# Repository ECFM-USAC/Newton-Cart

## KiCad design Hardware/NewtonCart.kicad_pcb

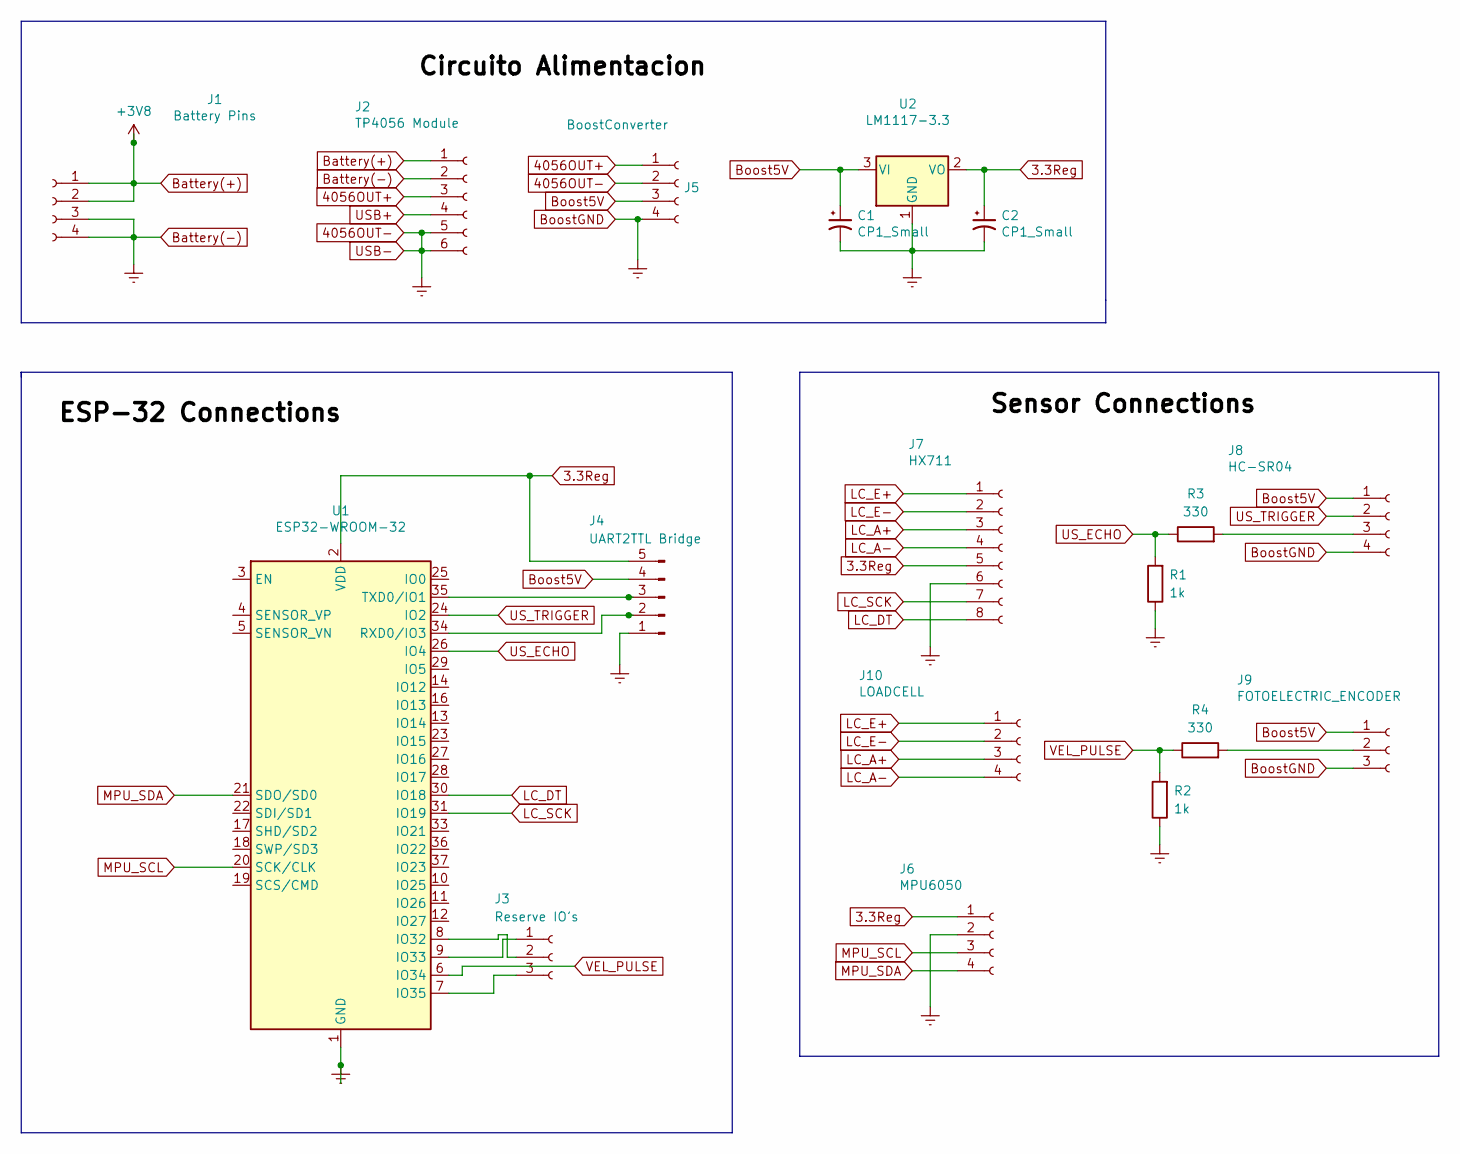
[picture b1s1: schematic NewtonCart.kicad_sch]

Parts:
C1, C2: CP1_Small; R_Axial_DIN0204_L3.6mm_D1.6mm_P5.08mm_Horizontal
J1: Battery Pins; PinHeader_1x04_P2.54mm_Vertical
J2: TP4056 Module; 18650 TP4056 Module
J3: Reserve IO's; PinHeader_1x03_P2.54mm_Vertical
J4: UART2TTL Bridge; PinHeader_1x05_P2.54mm_Vertical
J5: BoostConverter; 5-12V BoostConverter
J6: MPU6050; MPU 6050 Module
J7: HX711; HX711 Loadcell ADC
J8: HC-SR04; PinHeader_1x04_P2.54mm_Vertical
J9: FOTOELECTRIC_ENCODER; PinHeader_1x03_P2.54mm_Vertical
J10: LOADCELL; PinHeader_1x04_P2.54mm_Vertical
R1, R2: 1k; R_Axial_DIN0309_L9.0mm_D3.2mm_P12.70mm_Horizontal
R3, R4: 330; R_Axial_DIN0309_L9.0mm_D3.2mm_P12.70mm_Horizontal
U1: ESP32-WROOM-32
U2: LM1117-3.3; TO-220-3_Vertical

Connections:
3.3Reg: C2.1, J4.5, J6.1, J7.5, U1.2 (VDD), U2.2 (VO)
4056OUT+: J2.3, J5.1
4056OUT-: C1.2, C2.2, J1.3, J1.4, J2.2, J2.5, J2.6, J4.1, J5.2, J5.4, J6.2, J7.6, J8.4, J9.3, R1.1, R2.1, U1.1 (GND), U1.15 (GND), U1.38 (GND), U1.39 (GND), U2.1 (GND)
Battery(+): J1.1, J1.2, J2.1
Boost5V: C1.1, J4.4, J5.3, J8.1, J9.1, U2.3 (VI)
LC_A+: J7.3, J10.3
LC_A-: J7.4, J10.4
LC_DT: J7.8, U1.30 (IO18)
LC_E+: J7.1, J10.1
LC_E-: J7.2, J10.2
LC_SCK: J7.7, U1.31 (IO19)
MPU_SCL: J6.3, U1.20 (SCK/CLK)
MPU_SDA: J6.4, U1.21 (SDO/SD0)
unnamed: J3.3, U1.7 (IO35)
unnamed: J4.2, U1.34 (RXD0/IO3)
unnamed: J4.3, U1.35 (TXD0/IO1)
unnamed: J8.3, R3.2
unnamed: J9.2, R4.2
unnamed: J3.2, U1.8 (IO32)
unnamed: J3.1, U1.9 (IO33)
USB+: J2.4
US_ECHO: R1.2, R3.1, U1.26 (IO4)
US_TRIGGER: J8.2, U1.24 (IO2)
VEL_PULSE: R2.2, R4.1, U1.6 (IO34)

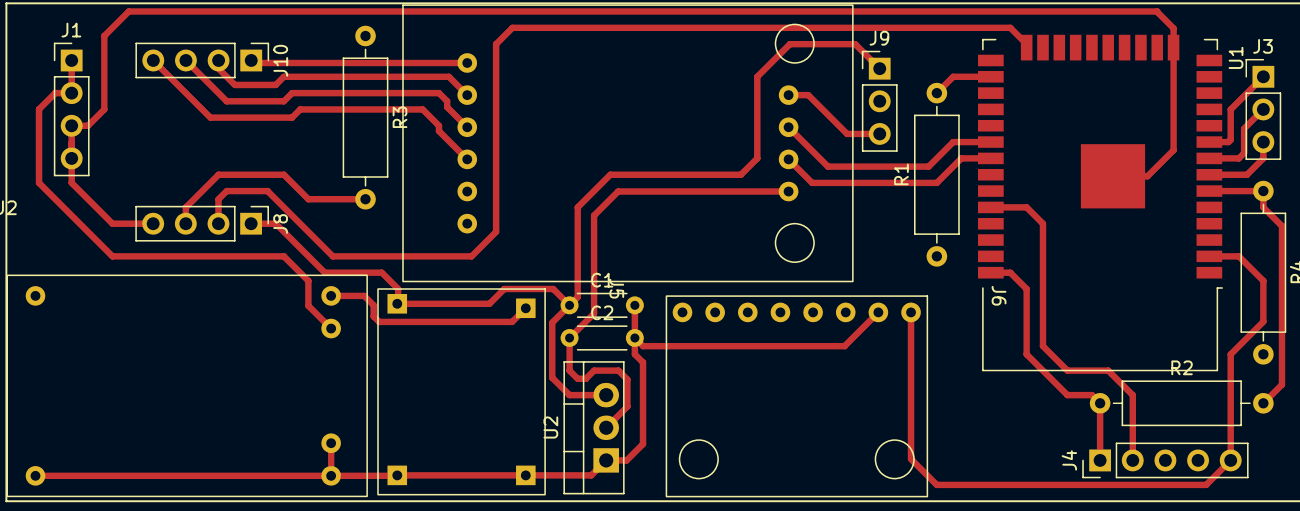
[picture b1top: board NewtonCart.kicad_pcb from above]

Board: 2 copper layers, 18 parts (0 on the bottom side), 23 nets.

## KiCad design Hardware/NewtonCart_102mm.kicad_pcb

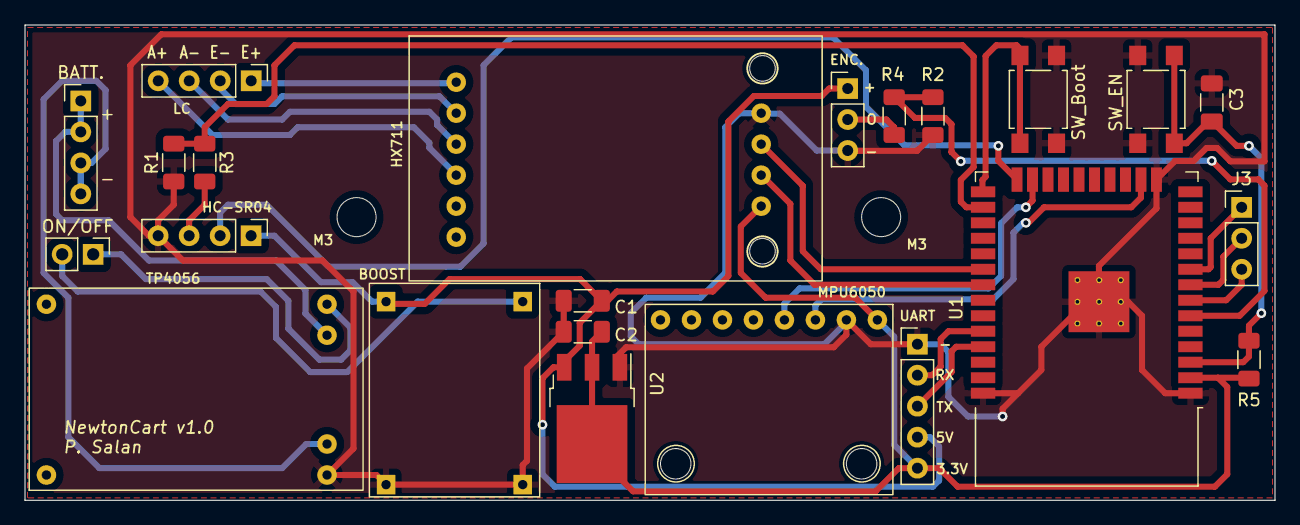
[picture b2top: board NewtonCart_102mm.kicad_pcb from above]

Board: 2 copper layers, 102.5 x 39.0 mm, 25 parts (0 on the bottom side), 27 nets.

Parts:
BATT.: Battery Pins; PinHeader_1x04_P2.54mm_Vertical
BOOST: BoostConverter; 5-12V BoostConverter
C1, C2: CP1_Small; C_1206_3216Metric_Pad1.33x1.80mm_HandSolder
C3: 10uF; C_1206_3216Metric_Pad1.33x1.80mm_HandSolder
ENC.: FOTOELECTRIC_ENCODER; PinHeader_1x03_P2.54mm_Vertical
HC-SR04: HC-SR04; PinHeader_1x04_P2.54mm_Vertical
HX711: HX711; HX711 Loadcell ADC
J3: Reserve IO's; PinHeader_1x03_P2.54mm_Vertical
LC: LOADCELL; PinHeader_1x04_P2.54mm_Vertical
M3, M3#2: MountingHole_3.2mm_M3
MPU6050: MPU6050; MPU 6050 Module
ON/OFF: ON/OFF-Switch; PinHeader_1x02_P2.54mm_Vertical
R1, R2: 1k; R_1206_3216Metric_Pad1.30x1.75mm_HandSolder
R3, R4: 330; R_1206_3216Metric_Pad1.30x1.75mm_HandSolder
R5: R; R_1206_3216Metric_Pad1.30x1.75mm_HandSolder
SW_Boot: SW_BOOT; SW_SPST_TL3305B
SW_EN: SW_Enable; SW_SPST_TL3305B
TP4056: TP4056 Module; 18650 TP4056 Module
U1: ESP32-WROOM-32
U2: LM1117-3.3; TO-252-3_TabPin2
UART: UART2TTL Bridge; PinHeader_1x05_P2.54mm_Vertical

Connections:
3.3Reg: C2.1, HX711.5, MPU6050.1, R5.1, U1.2 (VDD), U2.2 (VO), UART.5
4056OUT+: ON/OFF.1, TP4056.3
4056OUT-: BOOST.2, BOOST.4, C1.2, C2.2, C3.2, ENC..3, HC-SR04.4, HX711.6, MPU6050.2, R1.1, R2.1, SW_Boot.1, SW_EN.1, TP4056.5, U1.1 (GND), U1.15 (GND), U1.38 (GND), U1.39 (GND), U1.x, U2.1 (GND), UART.1
Battery(+): BATT..1, BATT..2, TP4056.1
Battery(-): BATT..3, BATT..4, TP4056.2
Boost5V: BOOST.3, C1.1, ENC..1, HC-SR04.1, U2.3 (VI), UART.4
LC_A+: HX711.3, LC.3
LC_A-: HX711.4, LC.4
LC_DT: HX711.8, U1.30 (IO18)
LC_E+: HX711.1, LC.1
LC_E-: HX711.2, LC.2
LC_SCK: HX711.7, U1.31 (IO19)
MPU_SCL: MPU6050.3, U1.16 (IO13)
MPU_SDA: MPU6050.4, U1.23 (IO15)
unnamed: C3.1, R5.2, SW_EN.2, U1.3 (EN)
unnamed: J3.1, U1.9 (IO33)
unnamed: J3.2, U1.8 (IO32)
unnamed: J3.3, U1.7 (IO35)
unnamed: U1.34 (RXD0/IO3), UART.2
unnamed: U1.35 (TXD0/IO1), UART.3
unnamed: HC-SR04.3, R3.2
unnamed: ENC..2, R4.2
unnamed: BOOST.1, ON/OFF.2
unnamed: SW_Boot.2, U1.25 (IO0)
US_ECHO: R1.2, R3.1, U1.26 (IO4)
US_TRIGGER: HC-SR04.2, U1.24 (IO2)
VEL_PULSE: R2.2, R4.1, U1.6 (IO34)

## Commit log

2020-10-11 10/10/2020 Update
    - Added some files required for the simulation.
    - Modified Carcasa1.ipt, improved HCR-04 Slot, added Robotlinking optical encoder module, and added a expected place and dimensions for the PCB.
    - Added ArmadoNewtonCart, with the changes listed above and the 4 bearing holders in position, this is the file expected to 3D print.
    - Pending: Place the slots for 18650 Battery and the TP4056 module in "Carcasa1".
2021-05-26 Actualización 25/05/21
2022-02-05 Prueba Commit 040222
2022-02-25 Antes 240222
2022-02-25 Anadido IMU MPU6050
2022-02-25 -Optical Encoder function and logic included.
2022-02-26 Updated Schematic
2022-03-02 Prueba Commit -Se añade archivo de pruebas BLe
2022-03-08 Created Netlist, Locating PCB Boart components. Some schematic changes.
2022-03-20 Cambios Placa al 190322
2022-06-05 Se añaden versiones creadas de PCB, nuevas modificaciones tanto en PCB como en esquemático. Se añade funcionalidad para Encendido/Apagado de la plataforma, se añade y se modifican botones de "Boot" y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
2022-07-26 Final Changes to 3D design, added battery base, PCB place remarked, ON/OFF Switch and charging microUSB Slots. New holes in rowlock bases for internal wiring. Updated NewtonCart firmware. New final c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
2022-09-16 Se añadieron modelos 3D de sensores que fueron utilizados para el análisis de centro de gravedad. Se añade funcionalidad RTOS en código Arduino Prototipo y programación funcional a este punto.
2025-01-31 FinalVersion(2024)
    Se suben archivos finales para construcción de NewtonCart
